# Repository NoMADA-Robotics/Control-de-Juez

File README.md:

# Control-de-Juez
Control remoto para el encendido y apagado con seguridad de los robots para competencia con tres obtones de preparación reset y go. Utliza un switch para encederlo y un led en la parte de abajo que se muestra desde arriba el estado y la transmisión de datos.
Utiliza el microcontrolador attiny1614, la serie 1 de Microchip por su versatilidad y buenos periféricos ademas de un bajo costo y muy fácil de programar con 
el pin de UPDI aunque se puede cambiar por culaquier otro.
Utiliza dos baterias cr2032 auque solo es necesario una pero al utilizar dos se meojora la descarga y el consumo.
El sentido de encedido de un prototipo es con READY, SET y GO en ese orden.
Será compatible con Nomada ingeniero maker y jsumo con un solo control sin necesidad de configuración.

Faltan probar algunas cosas y comenzare el firmware cuando tenga la placa porque probar en simulador no es muy kawai. Cualquier duda pueden contactarme en:
dzohl.yo@gmail.com

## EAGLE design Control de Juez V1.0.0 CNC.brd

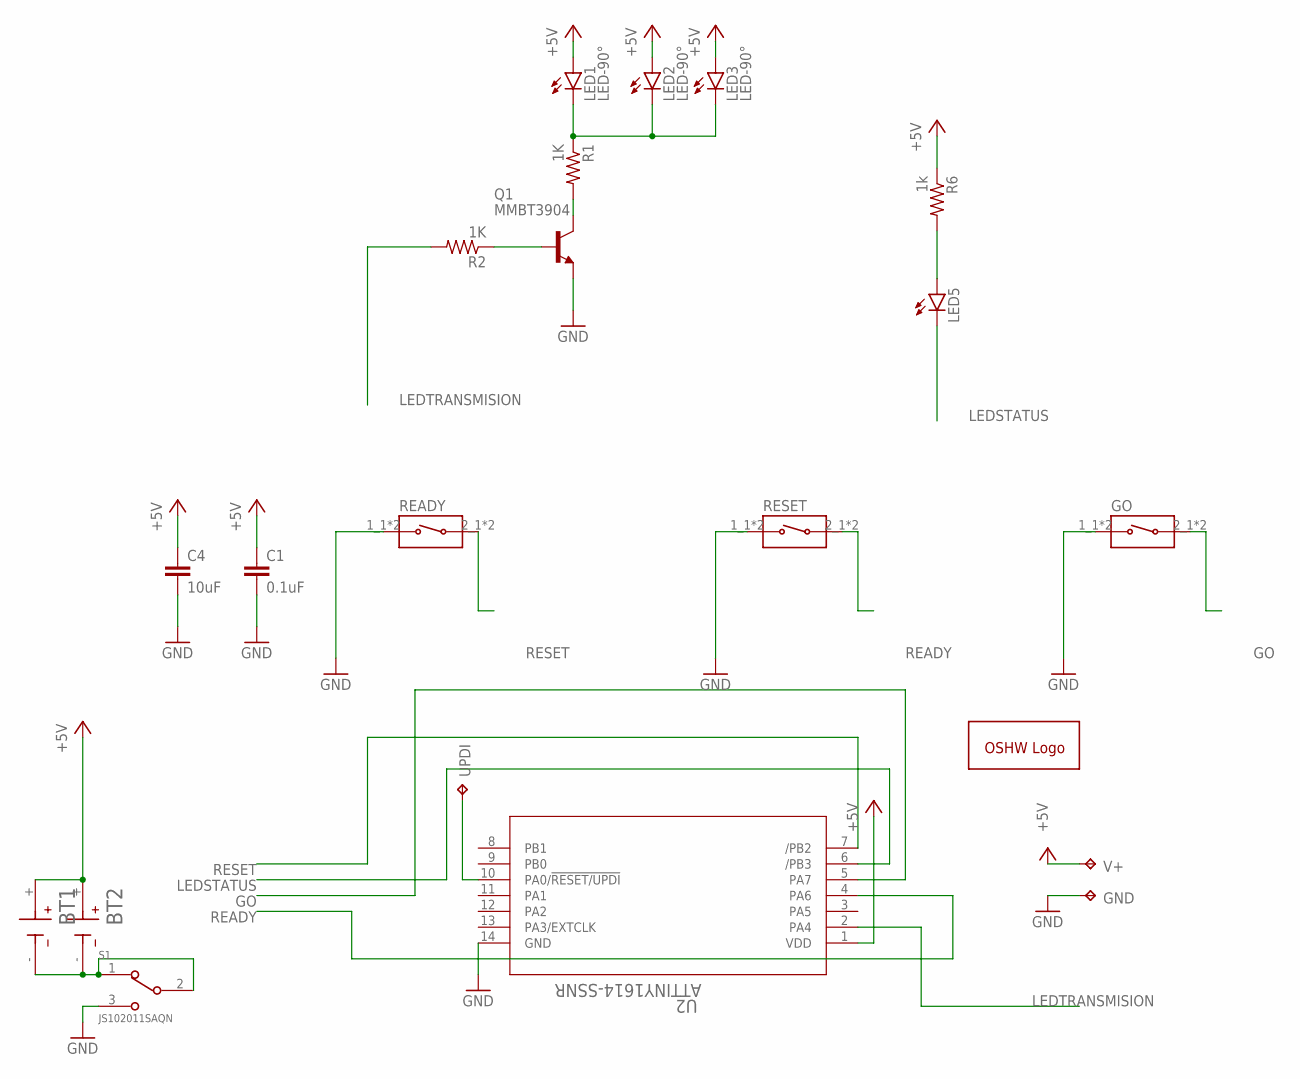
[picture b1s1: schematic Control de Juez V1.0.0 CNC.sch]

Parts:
BT1, BT2: BU2032SM-HD-G; BAT_BU2032SM-HD-G
C1: 0.1uF; C0603
C4: 10uF; C0603
GND: TPB1,27; B1,27
GO: EVQ-P7L01P; SW_EVQ-P7L01P
GOLD_ORB_SM1: OSHWLOGOLOGO8MM; OSHW_8MM
LED1, LED2, LED3: LED-90°
LED5: LEDSML1206; SML1206
Q1: MMBT3904; SOT23
R1, R2: 1K; R0603
R6: 1k; R0603
READY: EVQ-P7L01P; SW_EVQ-P7L01P
RESET: EVQ-P7L01P; SW_EVQ-P7L01P
S1: JS102011SAQN; SW_JS102011SAQN
U2: ATTINY1614-SSNR; SOIC14_SL_MCH
UPDI: TPB1,27; B1,27
V+: TPB1,27; B1,27

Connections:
+5V: BT1.+, BT2.+, C1.1, C4.1, LED1.1 (A), LED2.1 (A), LED3.1 (A), R6.1, U2.1 (VDD), V+.TP
GND: C1.2, C4.2, GND.TP, GO.1_1 (1), GO.1_2 (1), Q1.E, READY.1_1 (1), READY.1_2 (1), RESET.1_1 (1), RESET.1_2 (1), S1.3, U2.14 (GND)
GO: GO.2_1 (2), GO.2_2 (2), U2.5 (PA7)
LEDSTATUS: LED5.C, U2.6 (/PB3)
LEDTRANSMISION: R2.2, U2.2 (PA4)
unnamed: BT1.-, BT2.-, S1.1, S1.2
unnamed: LED1.2 (C), LED2.2 (C), LED3.2 (C), R1.1
unnamed: Q1.C, R1.2
unnamed: Q1.B, R2.1
unnamed: LED5.A, R6.2
READY: RESET.2_1 (2), RESET.2_2 (2), U2.4 (PA6)
RESET: READY.2_1 (2), READY.2_2 (2), U2.7 (/PB2)
UPDI: U2.10 (PA0/!RESET/UPDI), UPDI.TP

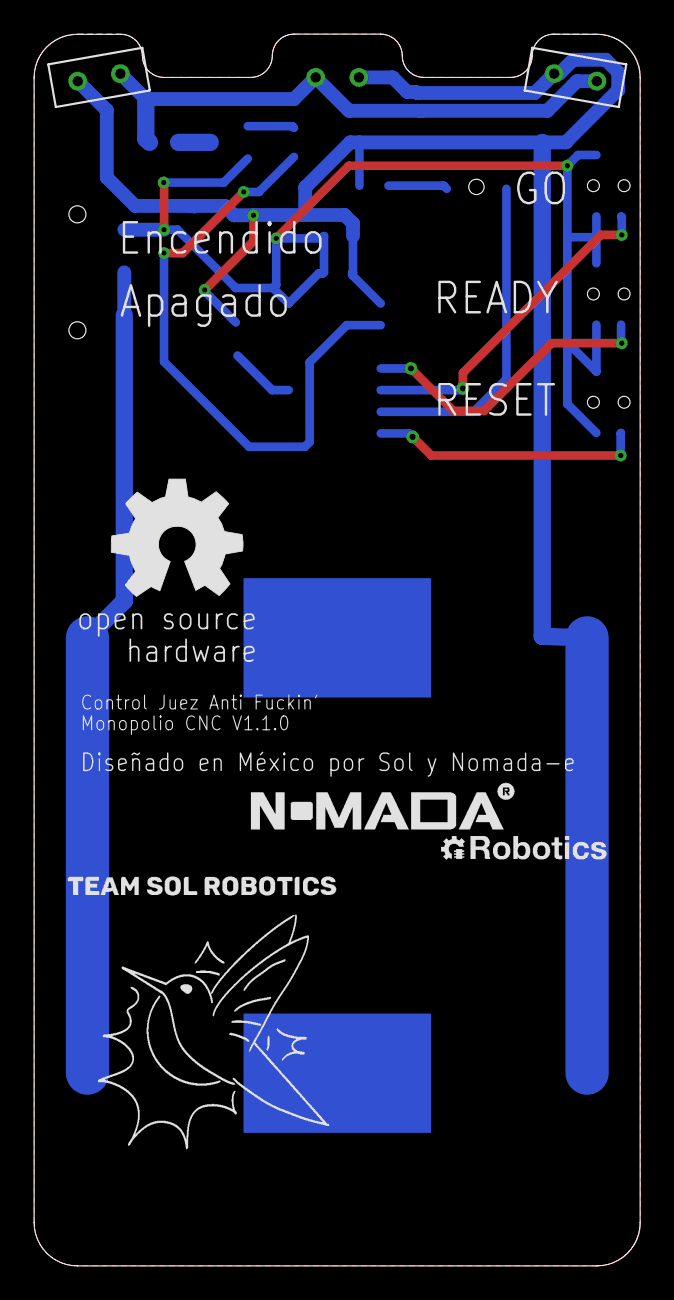
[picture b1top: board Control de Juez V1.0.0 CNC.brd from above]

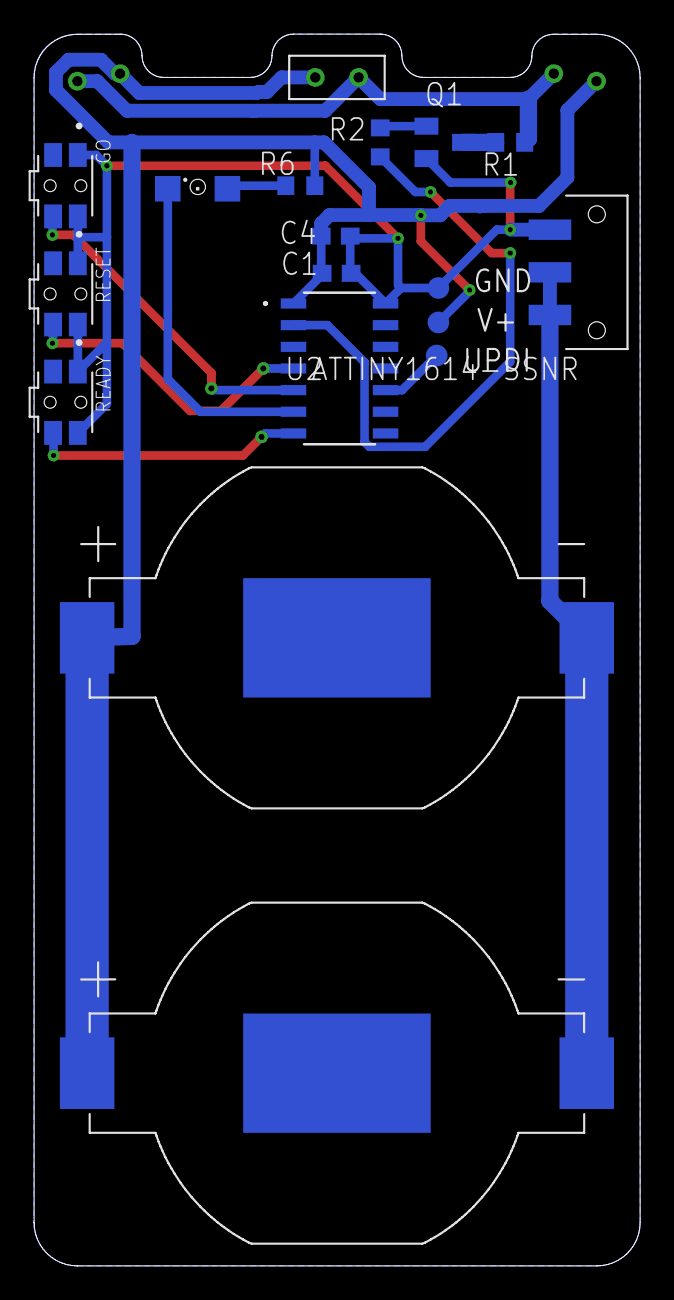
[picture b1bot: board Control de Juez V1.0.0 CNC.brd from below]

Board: 2 copper layers, 35.5 x 72.2 mm, 21 parts (18 on the bottom side), 13 nets.

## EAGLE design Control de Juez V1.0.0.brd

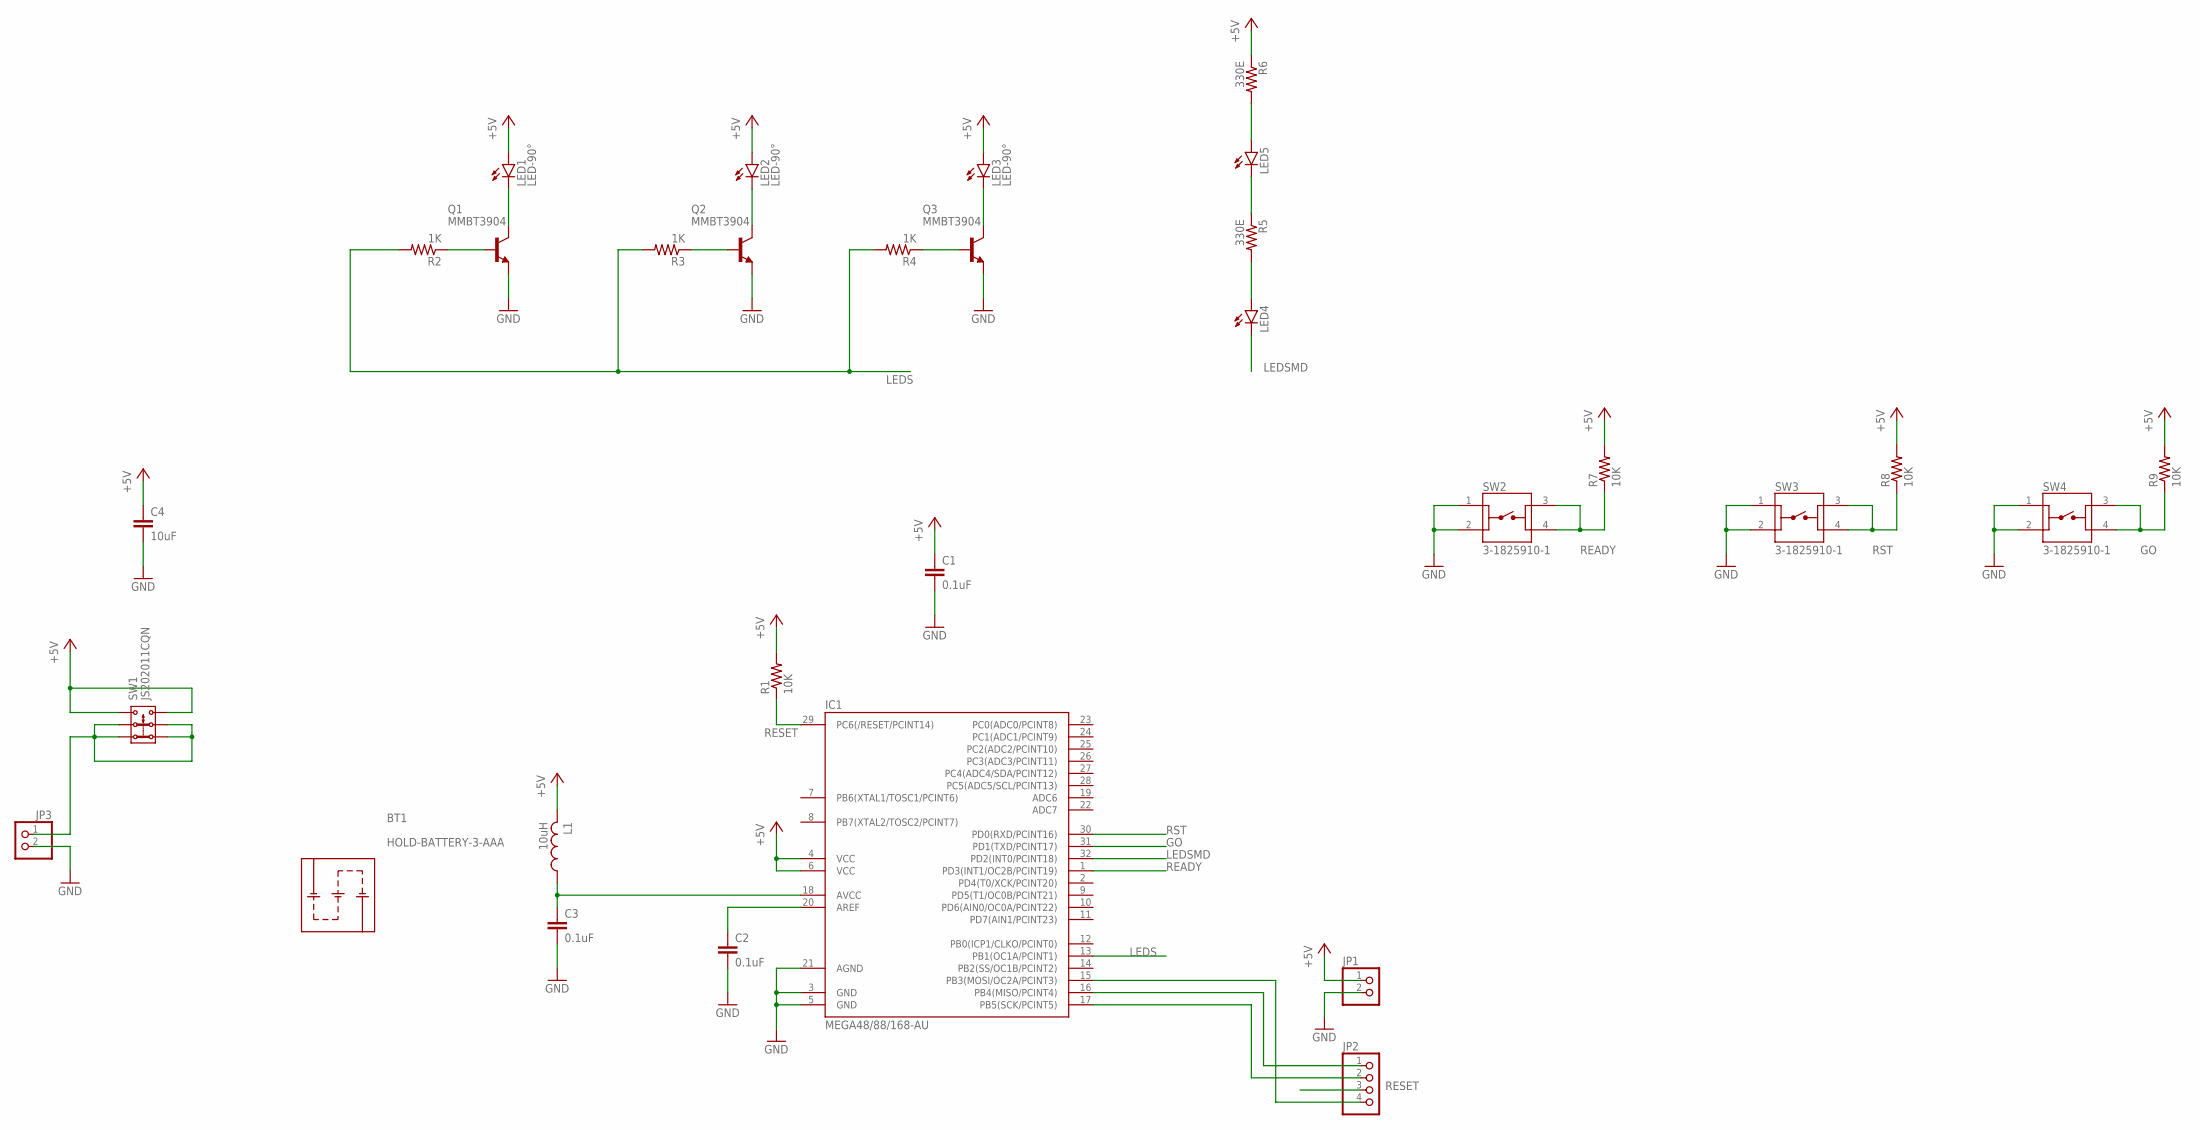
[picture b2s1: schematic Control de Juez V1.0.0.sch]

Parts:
BT1: HOLD-BATTERY-3-AAA; HOLDER-3-AAA
C1, C2, C3: 0.1uF; C0603
C4: 10uF; C0603
IC1: MEGA48/88/168-AU; TQFP32-08
JP1, JP3: PINHD-1X02_2.54-S; 1X02-S
JP2: PINHD-1X04_2.54-S; 1X04-S
L1: 10uH; L1812
LED1, LED2, LED3: LED-90°
LED4, LED5: LEDCHIP-LED0603; CHIP-LED0603
Q1, Q2, Q3: MMBT3904; SOT23
R1, R7, R8, R9: 10K; R0603
R2, R3, R4: 1K; R0603
R5, R6: 330E; R0603
SW1: JS202011CQN; PTH
SW2, SW3, SW4: 3-1825910-1; TE_3-1825910-1

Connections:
+5V: C1.1, C4.1, IC1.4 (VCC), IC1.6 (VCC), JP1.1, L1.2, LED1.1 (A), LED2.1 (A), LED3.1 (A), R1.2, R6.1, R7.2, R8.2, R9.2, SW1.3.1, SW1.3.2
GND: C1.2, C2.2, C3.2, C4.2, IC1.3 (GND), IC1.5 (GND), IC1.21 (AGND), JP1.2, JP3.2, Q1.E, Q2.E, Q3.E, SW2.1, SW2.2, SW3.1, SW3.2, SW4.1, SW4.2
GO: IC1.31 (PD1(TXD/PCINT17)), R9.1, SW4.3, SW4.4
LEDS: IC1.13 (PB1(OC1A/PCINT1)), R2.2, R3.2, R4.2
LEDSMD: IC1.32 (PD2(INT0/PCINT18)), LED4.C
unnamed: IC1.15 (PB3(MOSI/OC2A/PCINT3)), JP2.4
unnamed: C3.1, IC1.18 (AVCC), L1.1
unnamed: C2.1, IC1.20 (AREF)
unnamed: IC1.16 (PB4(MISO/PCINT4)), JP2.1
unnamed: IC1.17 (PB5(SCK/PCINT5)), JP2.2
unnamed: JP3.1, SW1.1.1, SW1.1.2, SW1.2.1, SW1.2.2
unnamed: LED1.2 (C), Q1.C
unnamed: LED2.2 (C), Q2.C
unnamed: LED3.2 (C), Q3.C
unnamed: Q3.B, R4.1
unnamed: Q2.B, R3.1
unnamed: Q1.B, R2.1
unnamed: LED5.C, R5.1
unnamed: LED5.A, R6.2
unnamed: LED4.A, R5.2
READY: IC1.1 (PD3(INT1/OC2B/PCINT19)), R7.1, SW2.3, SW2.4
RESET: IC1.29 (PC6(/RESET/PCINT14)), JP2.3, R1.1
RST: IC1.30 (PD0(RXD/PCINT16)), R8.1, SW3.3, SW3.4

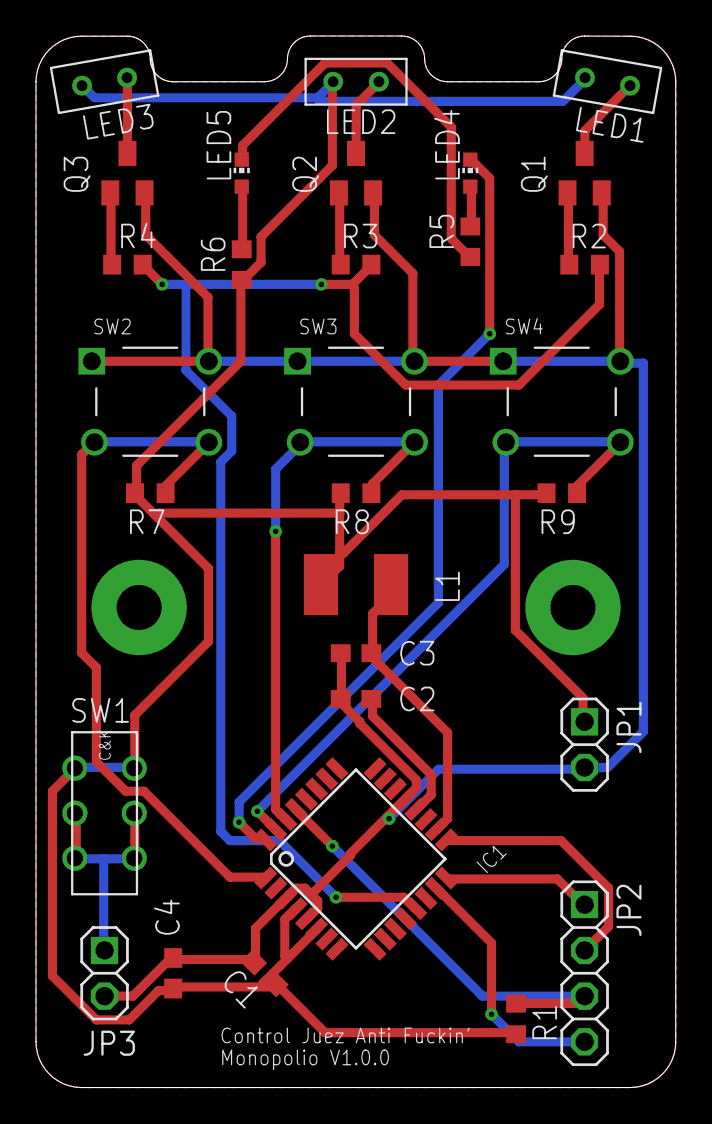
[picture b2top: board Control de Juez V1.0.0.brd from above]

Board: 2 copper layers, 35.5 x 58.4 mm, 31 parts (0 on the bottom side), 23 nets.

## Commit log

2021-02-28 Add files via upload
    Lista de material organizada
2021-03-02 Create firmware
2021-03-02 Add files via upload
    Código para trabajar en lo que lo termino
2021-03-02 Add files via upload
    Reconexiones para mejor programación ocupando el hardware del microcontrolador
2021-03-16 Gerber files
    Los gerber necesarios para la fabricación de la tarjeta
2021-04-04 Update main.c
    Contantes corregidas a los nuevos pines y probados hasta esta parte, es el setup
2021-04-05 Add files via upload
    No se porque no se subió antes y no me aviso

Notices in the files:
parts and their libraries:
COPYRIGHT: Copyright (C) 2018 Accelerated Designs. All rights reserved
